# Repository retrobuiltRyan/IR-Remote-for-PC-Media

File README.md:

# IR-Remote-for-PC-Media
Custom PCB + code for multi app media PC control with generic IR remote. Use an Arduino Pro Micro or RP2040 Pro Micro to decode an IR remote, assign macros. 
Control your PC with a USB HID (keyboard) device using an IR remote.
https://youtu.be/KI53avHp_a4

### Bill of Materials

| Reference         | Value                | Qty | Cost Each | Line Total | DigiKey P/N         | AliExpress Link                                                                 |
|------------------|----------------------|-----|------------|-------------|----------------------|----------------------------------------------------------------------------------|
| C1, C2, C3, C4, C5| 0.1uF 50V            | 5   | $0.07      | $0.35       | 1276-1068-1-ND        |                                                                                  |
| D1, D2, D3, D4, D5| WS2812B              | 5   | $0.10      | $0.50       | 1568-16347CT-ND    | [AliExpress](https://www.aliexpress.us/item/3256802466699315.html)             |
| J3               | OLED 1.3" 128x64     | 1   | $4.59      | $4.59       |                      | [AliExpress](https://www.aliexpress.us/item/3256806824217573.html)             |
| R1               | 220 ohm              | 1   | $0.02      | $0.02       | 311-220FRCT-ND        |                                                                                  |
| SW1              | SW Push Button       | 1   | $0.12      | $0.12       | CKN12221-1-ND         |                                                                                  |
| U1               | Pro Micro ATMEGA 32u4| 1   | $4.29      | $4.29       |                      | [AliExpress](https://www.aliexpress.us/item/3256807158682738.html)             |
| PCB              | JLCPCB               | 1   | $0.30      | $0.30       |                      |                                                                                  |
| IR Receiver      | IR RX                | 1   | $0.11      | $0.11       |                      | [AliExpress](https://www.aliexpress.us/item/3256804608870666.html)             |
| Remote           | Roku Media Remote    | 1   | $2.67      | $2.67       |                      | [AliExpress](https://www.aliexpress.us/item/3256807266003591.html)             |

**Total Cost: $12.95**

Note: (The example code will not work if your main TV is a roku TV; you'll need to decode and program a different remote [brand/ protocol] than your TV).

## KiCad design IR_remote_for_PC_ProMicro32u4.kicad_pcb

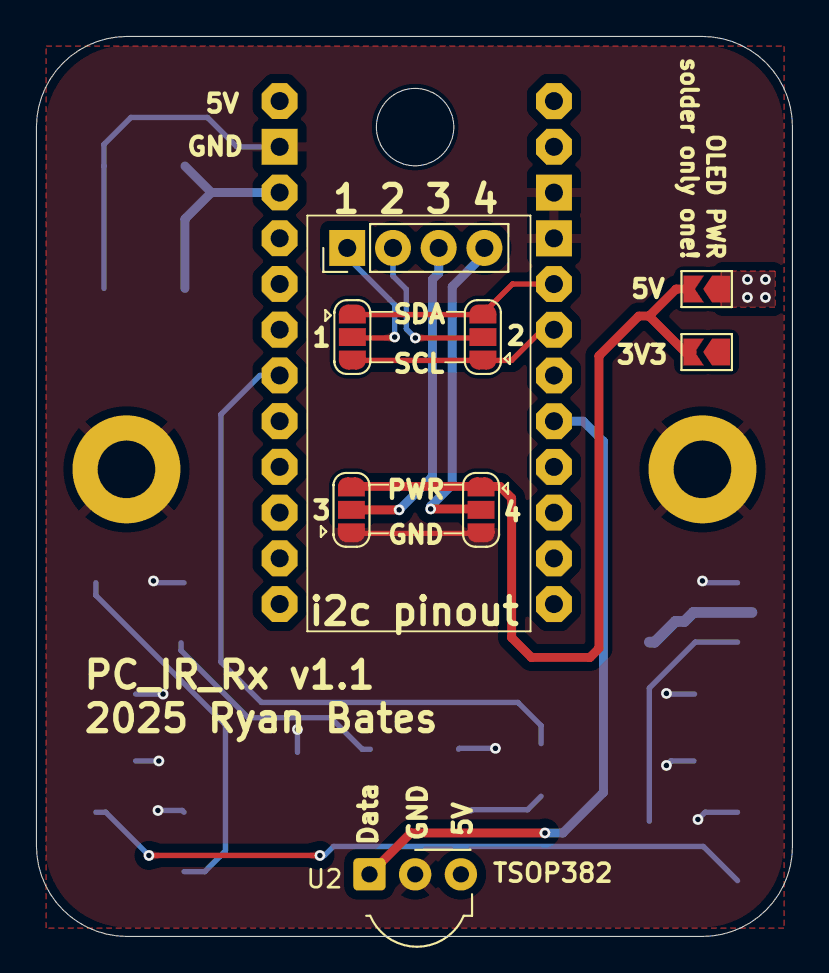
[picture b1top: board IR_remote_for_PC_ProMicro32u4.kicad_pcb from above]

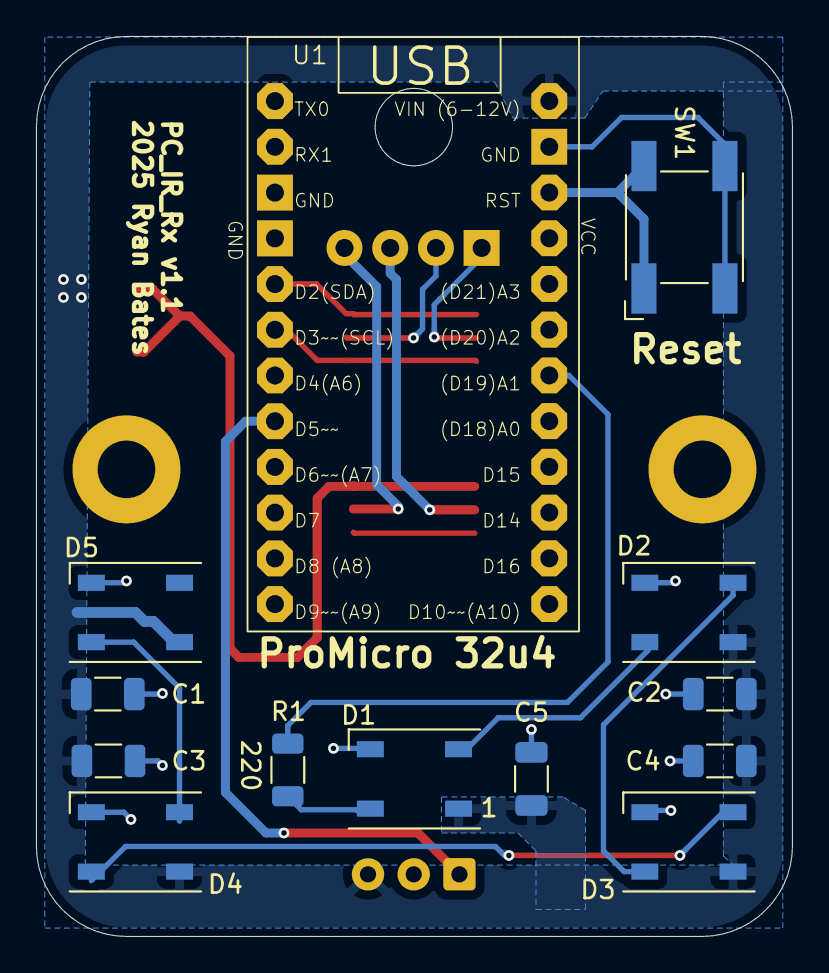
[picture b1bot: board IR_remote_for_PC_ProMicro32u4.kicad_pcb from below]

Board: 2 copper layers, 42.0 x 50.0 mm, 24 parts (13 on the bottom side), 17 nets.

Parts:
C1, C2, C3, C4, C5: 0.1uF 50V; C_1206_3216Metric
D1, D2, D3, D4, D5: WS2812B; LED_WS2812B_PLCC4_5.0x5.0mm_P3.2mm
H4: MountingHole; MountingHole_4.3mm_M4
H5, H6: MountingHole_M3_3.2mm_Pad; MountingHole_3.2mm_Pad
J1: PINHD_1x4_Male; PinHeader_1x04_P2.54mm_Vertical
JP1, JP2: SolderJumper_2_Open; SolderJumper-2_P1.3mm_Open_TrianglePad1.0x1.5mm
JP3, JP4, JP5, JP6: SolderJumper_3_Open; SolderJumper-3_P1.3mm_Open_RoundedPad1.0x1.5mm
R1: 220; R_1206_3216Metric
SW1: SW_Push; SW_SPST_Omron_B3FS-100xP
U1: Arduino_Pro_Micro_32u4
U2: TSDP341xx; Vishay_MOLD-3Pin

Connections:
+5V: C1.1, C2.1, C3.1, C4.1, C5.1, D1.1 (VDD), D2.1 (VDD), D3.1 (VDD), D4.1 (VDD), D5.1 (VDD), JP1.1 (A), U1.24 (RAW), U2.3 (Vs)
/1: J1.1, JP3.2 (C)
/2: J1.2, JP4.2 (C)
/3: J1.3, JP5.2 (C)
/4: J1.4, JP6.2 (C)
/DATA_IN: R1.2, U1.18 (A1)
/IR_DATA: U1.8 (D5), U2.1 (OUT)
/PWR: JP1.2 (B), JP2.2 (B), JP5.3 (B), JP6.3 (B)
/SCL: JP3.1 (A), JP4.1 (A), U1.6 (D3)
/SDA: JP3.3 (B), JP4.3 (B), U1.5 (D2)
GND: C1.2, C2.2, C3.2, C4.2, C5.2, D1.3 (VSS), D2.3 (VSS), D3.3 (VSS), D4.3 (VSS), D5.3 (VSS), H5.1, H6.1, JP5.1 (A), JP6.1 (A), SW1.2, U1.3 (GND), U1.4 (GND), U1.23 (GND), U2.2 (GND)
unnamed: D1.4 (DIN), R1.1
unnamed: D1.2 (DOUT), D2.4 (DIN)
unnamed: D2.2 (DOUT), D3.4 (DIN)
unnamed: D3.2 (DOUT), D4.4 (DIN)
unnamed: D4.2 (DOUT), D5.4 (DIN)
unnamed: SW1.1, U1.22 (RST)

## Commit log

2025-08-23 Code
    Drop all these files into a folder named "IR_remote_for_PC_ProMicro32u4".
2025-08-23 KiCAD design files
2025-08-23 PCB assembly .step
2025-08-23 Gerbers
    for JLCPCB
2025-08-23 3D Print case
2025-08-23 Add files via upload
    inkscape file
2025-08-23 Code
2025-08-23 Profile planning diagram
    inkscape
2025-10-17 Create LICENSE
